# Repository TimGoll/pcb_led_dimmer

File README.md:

# NE555 LED Strip Dimmer

This PCB is designed to dim the light of 12V led strips. It can also be used to control other types of 12V devices, such as PC fans.

It is designed around [this potentiometer](https://www.ebay.de/itm/123801827169) that has a builtin switch. This way only one input is needed to turn the light on.

**Note:** The markings for the two diodes are inverted.

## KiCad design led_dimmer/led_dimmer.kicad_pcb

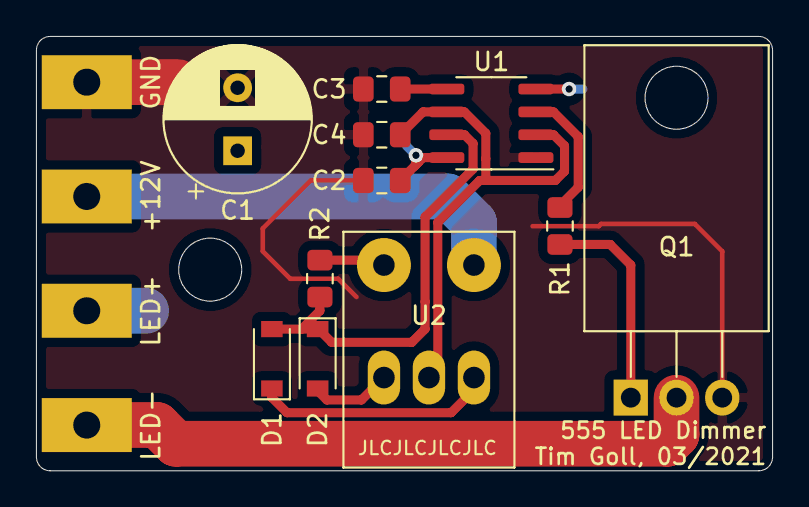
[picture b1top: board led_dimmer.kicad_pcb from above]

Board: 2 copper layers, 40.9 x 24.1 mm, 15 parts (0 on the bottom side), 11 nets.

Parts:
+12V: +12V_in; solder_pad_5x3
C1: 470u; CP_Radial_D8.0mm_P3.50mm
C2, C4: 100n; C_0805_2012Metric_Pad1.15x1.40mm_HandSolder
C3: 10n; C_0805_2012Metric_Pad1.15x1.40mm_HandSolder
D1, D2: D_Small; D_SOD-123
GND: GND_in; solder_pad_5x3
LED+: LED+; solder_pad_5x3
LED-: LED-; solder_pad_5x3
Q1: BUZ11; TO-220-3_Horizontal_TabDown
R1: 10k; R_0805_2012Metric_Pad1.15x1.40mm_HandSolder
R2: 1k; R_0805_2012Metric_Pad1.15x1.40mm_HandSolder
U1: NE555D; SOIC-8_3.9x4.9mm_P1.27mm
U2: 50k; poti_switch_mono

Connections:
12V_int: C1.1, C2.1, LED+.1, R2.1, U1.4, U1.8, U2.4
+12V: +12V.1, U2.5
GND: C1.2, C2.2, C3.2, C4.2, GND.1, Q1.3, U1.1
unnamed: C3.1, U1.5
unnamed: C4.1, U1.2, U1.6, U2.2
unnamed: D1.1, U2.3
unnamed: D1.2, D2.1, R2.2, U1.7
unnamed: D2.2, U2.1
unnamed: LED-.1, Q1.2
unnamed: Q1.1, R1.1
unnamed: R1.2, U1.3

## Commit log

2021-03-11 finished pcb
2021-03-12 small pcb update
2021-04-13 created gerber files
2022-02-15 added housing
